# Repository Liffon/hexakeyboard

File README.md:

# Schematic for a hexalinear keyboard PCB

This is a KiCad project for a hexalinear keyboard PCB using a breakout Proton C as a controller.

Required libraries:

- [`kicad_lib_tmk`](https://github.com/tmk/kicad_lib_tmk)
- [`qmk_hardware`](https://github.com/qmk/qmk_hardware)

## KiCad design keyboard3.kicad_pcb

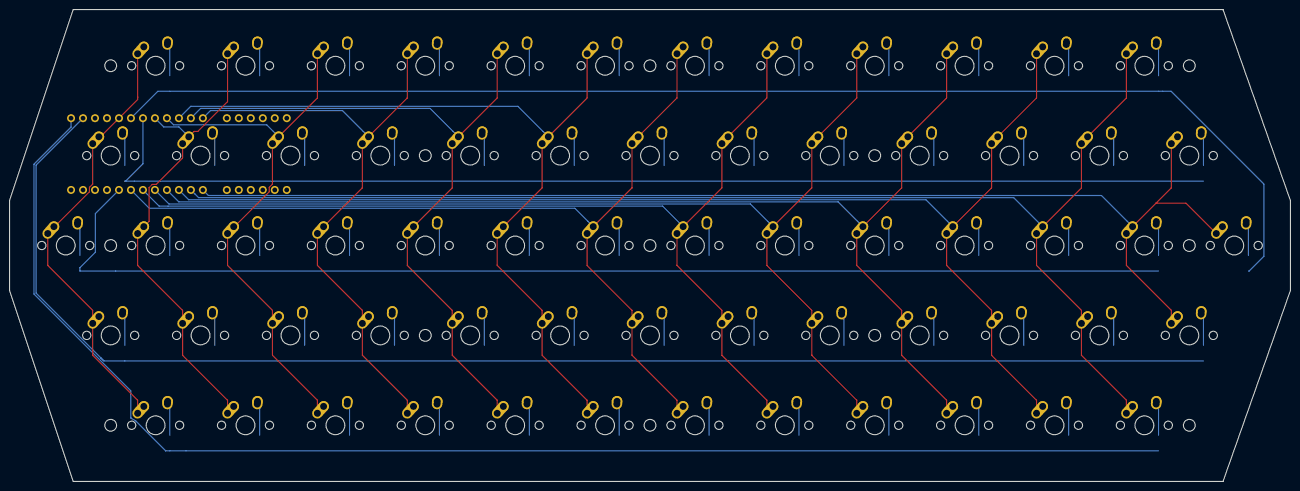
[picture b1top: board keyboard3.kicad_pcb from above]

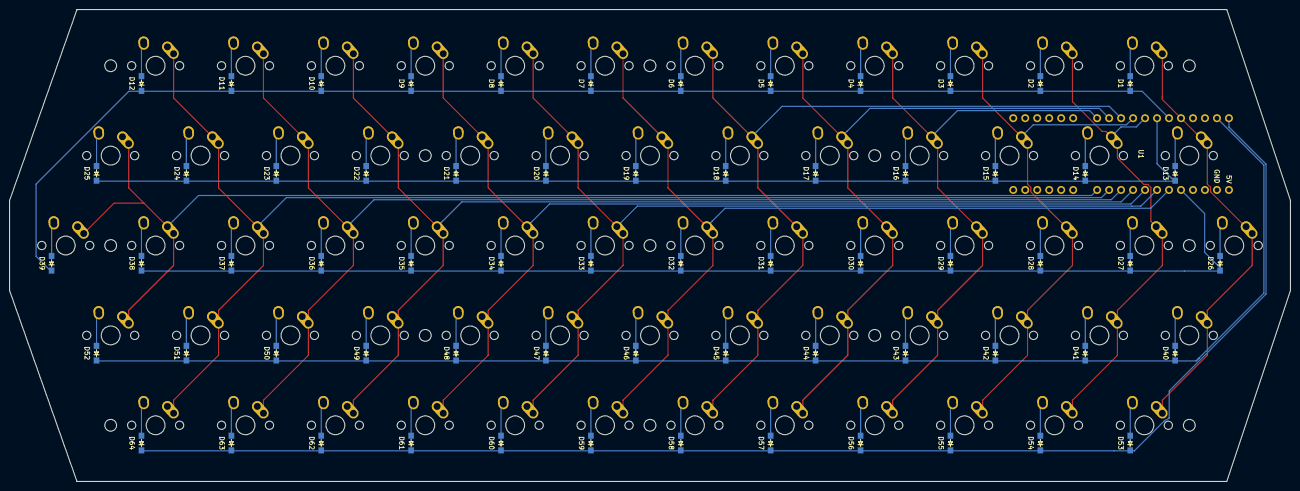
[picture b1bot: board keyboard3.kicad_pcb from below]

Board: 2 copper layers, 271.5 x 100.0 mm, 129 parts (65 on the bottom side), 82 nets.

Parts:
D1, D2, D3, D4, D5, D6, D7, D8, D9, D10, D11, D12, D13, D14, D15, D16, D17, D18, D19, D20, D21, D22, D23, D24, D25, D26, D27, D28, D29, D30, D31, D32, D33, D34, D35, D36, D37, D38, D39, D40, D41, D42, D43, D44, D45, D46, D47, D48, D49, D50, D51, D52, D53, D54, D55, D56, D57, D58, D59, D60, D61, D62, D63, D64: SOD-123; D_SOD-123_Hand_solder
MX1, MX2, MX3, MX4, MX5, MX6, MX7, MX8, MX9, MX10, MX11, MX12, MX13, MX14, MX15, MX16, MX17, MX18, MX19, MX20, MX21, MX22, MX23, MX24, MX25, MX26, MX27, MX28, MX29, MX30, MX31, MX32, MX33, MX34, MX35, MX36, MX37, MX38, MX39, MX40, MX41, MX42, MX43, MX44, MX45, MX46, MX47, MX48, MX49, MX50, MX51, MX52, MX53, MX54, MX55, MX56, MX57, MX58, MX59, MX60, MX61, MX62, MX63, MX64: MX-NoLED; MX-1U-NoLED
U1: proton_c; proton_c_holes_only

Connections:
COL0: MX1.1, MX13.1, MX26.1, MX40.1, MX53.1, U1.B7
COL1: MX2.1, MX14.1, MX27.1, MX41.1, MX54.1, U1.B4
COL2: MX3.1, MX15.1, MX28.1, MX42.1, MX55.1, U1.B3
COL3: MX4.1, MX16.1, MX29.1, MX43.1, MX56.1, U1.B0
COL4: MX5.1, MX17.1, MX30.1, MX44.1, MX57.1, U1.B1
COL5: MX6.1, MX18.1, MX31.1, MX45.1, MX58.1, U1.B2
COL6: MX7.1, MX19.1, MX32.1, MX46.1, MX59.1, U1.A1
COL7: MX8.1, MX20.1, MX33.1, MX47.1, MX60.1, U1.A0
COL8: MX9.1, MX21.1, MX34.1, MX48.1, MX61.1, U1.B8
COL9: MX10.1, MX22.1, MX35.1, MX49.1, MX62.1, U1.B13
COL10: MX11.1, MX23.1, MX36.1, MX50.1, MX63.1, U1.B14
COL11: MX12.1, MX24.1, MX37.1, MX51.1, MX64.1, U1.B15
COL12: MX25.1, MX38.1, MX39.1, MX52.1, U1.B9
unnamed: D1.2, MX1.2
unnamed: D2.2, MX2.2
unnamed: D3.2, MX3.2
unnamed: D4.2, MX4.2
unnamed: D5.2, MX5.2
unnamed: D6.2, MX6.2
unnamed: D7.2, MX7.2
unnamed: D8.2, MX8.2
unnamed: D9.2, MX9.2
unnamed: D10.2, MX10.2
unnamed: D11.2, MX11.2
unnamed: D12.2, MX12.2
unnamed: D13.2, MX13.2
unnamed: D14.2, MX14.2
unnamed: D15.2, MX15.2
unnamed: D16.2, MX16.2
unnamed: D17.2, MX17.2
unnamed: D18.2, MX18.2
unnamed: D19.2, MX19.2
unnamed: D20.2, MX20.2
unnamed: D21.2, MX21.2
unnamed: D22.2, MX22.2
unnamed: D23.2, MX23.2
unnamed: D24.2, MX24.2
unnamed: D25.2, MX25.2
unnamed: D26.2, MX26.2
unnamed: D27.2, MX27.2
unnamed: D28.2, MX28.2
unnamed: D29.2, MX29.2
unnamed: D30.2, MX30.2
unnamed: D31.2, MX31.2
unnamed: D32.2, MX32.2
unnamed: D33.2, MX33.2
unnamed: D34.2, MX34.2
unnamed: D35.2, MX35.2
unnamed: D36.2, MX36.2
unnamed: D37.2, MX37.2
unnamed: D38.2, MX38.2
unnamed: D39.2, MX39.2
unnamed: D40.2, MX40.2
unnamed: D41.2, MX41.2
unnamed: D42.2, MX42.2
unnamed: D43.2, MX43.2
unnamed: D44.2, MX44.2
unnamed: D45.2, MX45.2
unnamed: D46.2, MX46.2
unnamed: D47.2, MX47.2
unnamed: D48.2, MX48.2
unnamed: D49.2, MX49.2
unnamed: D50.2, MX50.2
unnamed: D51.2, MX51.2
unnamed: D52.2, MX52.2
unnamed: D53.2, MX53.2
unnamed: D54.2, MX54.2
unnamed: D55.2, MX55.2
unnamed: D56.2, MX56.2
unnamed: D57.2, MX57.2
unnamed: D58.2, MX58.2
unnamed: D59.2, MX59.2
unnamed: D60.2, MX60.2
unnamed: D61.2, MX61.2
unnamed: D62.2, MX62.2
unnamed: D63.2, MX63.2
unnamed: D64.2, MX64.2
ROW0: D1.1, D2.1, D3.1, D4.1, D5.1, D6.1, D7.1, D8.1, D9.1, D10.1, D11.1, D12.1, D39.1, U1.B6
ROW1: D13.1, D14.1, D15.1, D16.1, D17.1, D18.1, D19.1, D20.1, D21.1, D22.1, D23.1, D24.1, D25.1, U1.B5
ROW2: D26.1, D27.1, D28.1, D29.1, D30.1, D31.1, D32.1, D33.1, D34.1, D35.1, D36.1, D37.1, D38.1, U1.A2
ROW3: D40.1, D41.1, D42.1, D43.1, D44.1, D45.1, D46.1, D47.1, D48.1, D49.1, D50.1, D51.1, D52.1, U1.A10
ROW4: D53.1, D54.1, D55.1, D56.1, D57.1, D58.1, D59.1, D60.1, D61.1, D62.1, D63.1, D64.1, U1.A9

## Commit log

2020-04-30 Dump into Git
2020-04-30 Foundation for a case in OpenSCAD
